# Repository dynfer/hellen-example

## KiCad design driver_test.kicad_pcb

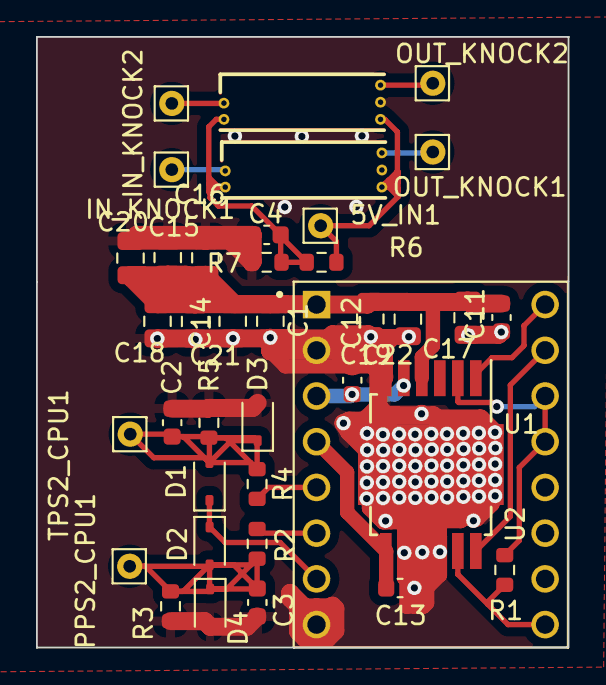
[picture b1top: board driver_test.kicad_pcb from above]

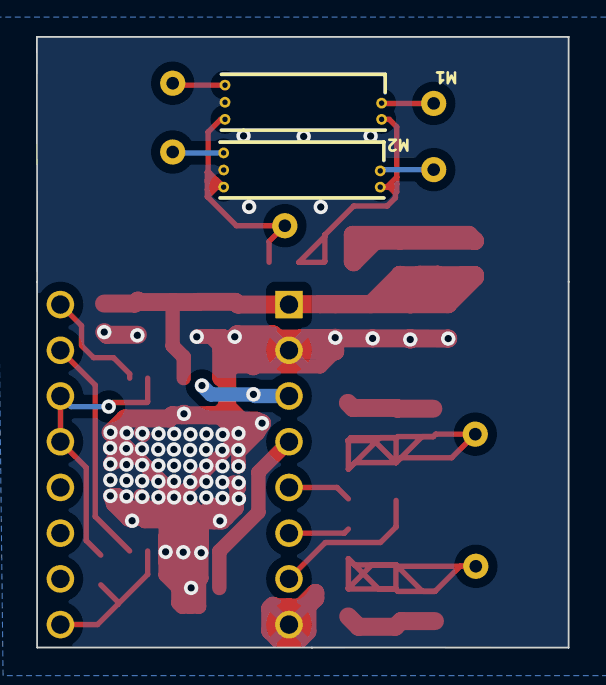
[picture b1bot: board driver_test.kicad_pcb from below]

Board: 4 copper layers, 29.5 x 33.9 mm, 38 parts (2 on the bottom side), 18 nets.

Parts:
5V_IN1: Pad; Pin_D0.7mm_L6.5mm_W1.8mm_FlatFork
C1, C14, C15, C16, C17, C18, C19, C20, C21, C22: 10u; C_0805_2012Metric
C2, C3: 22nF; C_0603_1608Metric
C4: 2.2uF; C_0603_1608Metric
C11: 100n; C_0603_1608Metric
C12, C13: 10n; C_0603_1608Metric
D1, D2, D3, D4: 1N5819WS; D_SOD-323
IN_KNOCK1, IN_KNOCK2: Pad; Pin_D0.7mm_L6.5mm_W1.8mm_FlatFork
M1, M2: Module-knock-0.2; knock
OUT_KNOCK1, OUT_KNOCK2: Pad; Pin_D0.7mm_L6.5mm_W1.8mm_FlatFork
PPS2_CPU1: Pad; Pin_D0.7mm_L6.5mm_W1.8mm_FlatFork
R1: 4.7k; R_0603_1608Metric
R2, R4: 4.7K; R_0603_1608Metric
R3, R5: 9.1K; R_0603_1608Metric
R6, R7: 510; R_0603_1608Metric
TPS2_CPU1: Pad; Pin_D0.7mm_L6.5mm_W1.8mm_FlatFork
U1: A4988_STEPPER_MOTOR_DRIVER_CARRIER; MODULE_A4988_STEPPER_MOTOR_DRIVER_CARRIER
U2: TLE9201SG; Infineon_PG-DSO-12-11

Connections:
+3.3V: D1.1 (K), D2.1 (K), R1.2, U1.7 (STEP), U1.13 (2A), U1.14 (2B), U2.2 (VSO)
+5V: 5V_IN1.1, M1.E1 (V5A), M2.E1 (V5A), R6.1
+12VA: C1.2, C11.2, C14.2, C15.2, C16.2, C17.2, C18.2, C19.2, C20.2, C21.2, C22.2, U1.1 (~ENABLE), U2.4 (VS)
/DIR: U1.16 (VMOT), U2.1 (DIR)
/DIS: R1.1, U1.9 (GND), U2.11 (DIS)
/OUT+: C13.2, U1.4 (MS3), U2.7 (OUT2)
/OUT-: C12.2, U1.3 (MS2), U2.5 (OUT1)
/PPS2_IN: R2.2, U1.6 (~SLEEP)
/PWM: U1.15 (GND), U2.12 (PWM)
/TPS2_IN: R4.2, U1.5 (~RESET)
/VREF: C4.2, M1.W2 (VREF), M2.W2 (VREF), R6.2, R7.1
GND: C1.1, C2.1, C3.1, C4.1, C11.1, C12.1, C13.1, C14.1, C15.1, C16.1, C17.1, C18.1, C19.1, C20.1, C21.1, C22.1, D3.2 (A), D4.2 (A), M1.E2 (GND), M2.E2 (GND), R3.1, R5.1, R7.2, U1.2 (MS1), U1.8 (DIR), U2.6 (GND), U2.8 (SI), U2.9 (CSN), U2.10 (SCK), U2.13 (GND)
unnamed: C2.2, D1.2 (A), D3.1 (K), R4.1, R5.2, TPS2_CPU1.1
unnamed: C3.2, D2.2 (A), D4.1 (K), PPS2_CPU1.1, R2.1, R3.2
unnamed: IN_KNOCK1.1, M2.W1 (IN_KNOCK)
unnamed: IN_KNOCK2.1, M1.W1 (IN_KNOCK)
unnamed: M1.E3 (OUT_KNOCK), OUT_KNOCK2.1
unnamed: M2.E3 (OUT_KNOCK), OUT_KNOCK1.1

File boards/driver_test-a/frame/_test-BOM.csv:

Comment,Designator,Footprint,LCSC Part #
"Pad","5V_IN1","Pin_D0.7mm_L6.5mm_W1.8mm_FlatFork",""
"10u","C1","C0805","C15850"
"22nF","C2","C0603",""
"22nF","C3","C0603",""
"2.2uF","C4","C0603",""
"100n","C11","C0603","C14663"
"10n","C12","C0603","C57112"
"10n","C13","C0603","C57112"
"10u","C14","C0805","C15850"
"10u","C15","C0805","C15850"
"10u","C16","C0805","C15850"
"10u","C17","C0805","C15850"
"10u","C18","C0805","C15850"
"10u","C19","C0805","C15850"
"10u","C20","C0805","C15850"
"10u","C21","C0805","C15850"
"10u","C22","C0805","C15850"
"1N5819WS","D1","D_SOD-323",""
"1N5819WS","D2","D_SOD-323",""
"1N5819WS","D3","D_SOD-323",""
"1N5819WS","D4","D_SOD-323",""
"Pad","IN_KNOCK1","Pin_D0.7mm_L6.5mm_W1.8mm_FlatFork",""
"Pad","IN_KNOCK2","Pin_D0.7mm_L6.5mm_W1.8mm_FlatFork",""
"Module:knock/0.2","M1","knock",""
"Module:knock/0.2","M2","knock",""
"Pad","OUT_KNOCK1","Pin_D0.7mm_L6.5mm_W1.8mm_FlatFork",""
"Pad","OUT_KNOCK2","Pin_D0.7mm_L6.5mm_W1.8mm_FlatFork",""
"Pad","PPS2_CPU1","Pin_D0.7mm_L6.5mm_W1.8mm_FlatFork",""
"4.7k","R1","R0603","C23162"
"4.7K","R2","R0603",""
"9.1K","R3","R0603",""
"4.7K","R4","R0603",""
"9.1K","R5","R0603",""
"510","R6","R0603",""
"510","R7","R0603",""
"Pad","TPS2_CPU1","Pin_D0.7mm_L6.5mm_W1.8mm_FlatFork",""
"A4988_STEPPER_MOTOR_DRIVER_CARRIER","U1","MODULE_A4988_STEPPER_MOTOR_DRIVER_CARRIER",""
"TLE9201SG","U2","Infineon_PG-DSO-12-11","C112633"

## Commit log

2023-12-29 initial
2023-12-29 [skip actions] Auto-generated board
2023-12-29 initial5
2023-12-29 initial2
